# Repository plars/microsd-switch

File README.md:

## MicroSD Switch

This a derivative work of a similar project by Joel Fernandes.  You can find
his original works that this is based on at:
https://github.com/joelagnel/microsd-switch

The main changes I made were to use 2x4 IDC headers instead of 1x8 rows,
and I also removed the usb/ftdi based switching in favor of a 40pin
connector so that I could use it as a RPI2/3 hat. It's not a proper hat
layout at the moment with eeprom or recommended board layout because it's
a work in progress, but the prototypes fit nicely as it is now.

To switch between host and target, it is currently wired to use GPIO 12

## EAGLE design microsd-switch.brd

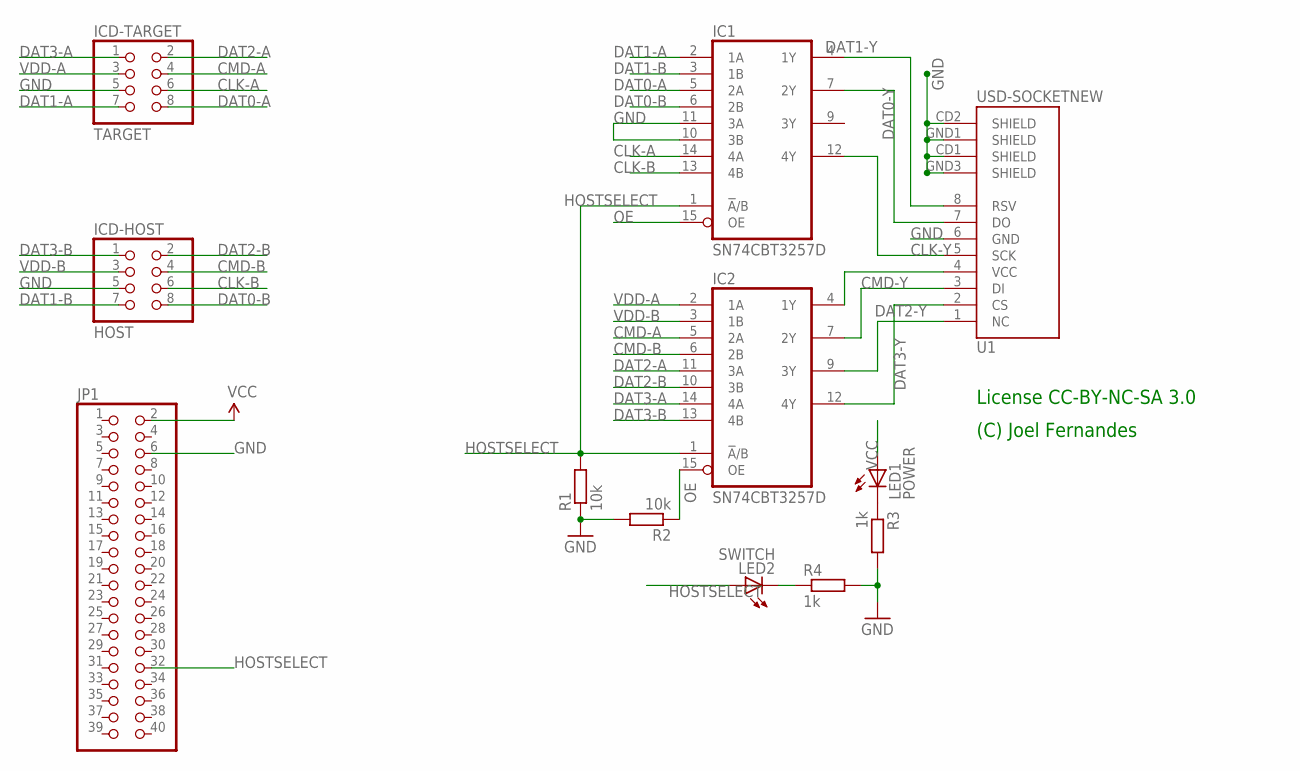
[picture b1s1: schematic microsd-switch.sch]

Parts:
IC1, IC2: SN74CBT3257D; SO16
ICD-HOST: HOST; 2X04
ICD-TARGET: TARGET; 2X04
JP1: PINHD-2X20; 2X20
LED1: POWER; CHIP-LED0805
LED2: SWITCH; CHIP-LED0805
R1, R2: 10k; R1206
R3, R4: 1k; R1206
U1: USD-SOCKETNEW; MICRO-SD-SOCKET-PP

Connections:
CLK-A: IC1.14 (4A), ICD-TARGET.6
CLK-B: IC1.13 (4B), ICD-HOST.6
CLK-Y: IC1.12 (4Y), U1.5 (SCK)
CMD-A: IC2.5 (2A), ICD-TARGET.4
CMD-B: IC2.6 (2B), ICD-HOST.4
CMD-Y: IC2.7 (2Y), U1.3 (DI)
DAT0-A: IC1.5 (2A), ICD-TARGET.8
DAT0-B: IC1.6 (2B), ICD-HOST.8
DAT0-Y: IC1.7 (2Y), U1.7 (DO)
DAT1-A: IC1.2 (1A), ICD-TARGET.7
DAT1-B: IC1.3 (1B), ICD-HOST.7
DAT1-Y: IC1.4 (1Y), U1.8 (RSV)
DAT2-A: IC2.11 (3A), ICD-TARGET.2
DAT2-B: IC2.10 (3B), ICD-HOST.2
DAT2-Y: IC2.9 (3Y), U1.1 (NC)
DAT3-A: IC2.14 (4A), ICD-TARGET.1
DAT3-B: IC2.13 (4B), ICD-HOST.1
DAT3-Y: IC2.12 (4Y), U1.2 (CS)
GND: IC1.8 (GND), IC1.10 (3B), IC1.11 (3A), IC2.8 (GND), ICD-HOST.5, ICD-TARGET.5, JP1.6, R1.1, R2.2, R3.2, R4.2, U1.6 (GND), U1.CD1 (SHIELD), U1.CD2 (SHIELD), U1.GND1 (SHIELD), U1.GND3 (SHIELD)
HOSTSELECT: IC1.1 (!A!/B), IC2.1 (!A!/B), JP1.32, LED2.A, R1.2
unnamed: IC2.4 (1Y), U1.4 (VCC)
unnamed: LED1.C, R3.1
unnamed: LED2.C, R4.1
OE: IC1.15 (OE), IC2.15 (OE), R2.1
VCC: IC1.16 (VCC), IC2.16 (VCC), JP1.2, LED1.A
VDD-A: IC2.2 (1A), ICD-TARGET.3
VDD-B: IC2.3 (1B), ICD-HOST.3

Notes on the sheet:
License CC-BY-NC-SA 3.0
(C) Joel Fernandes

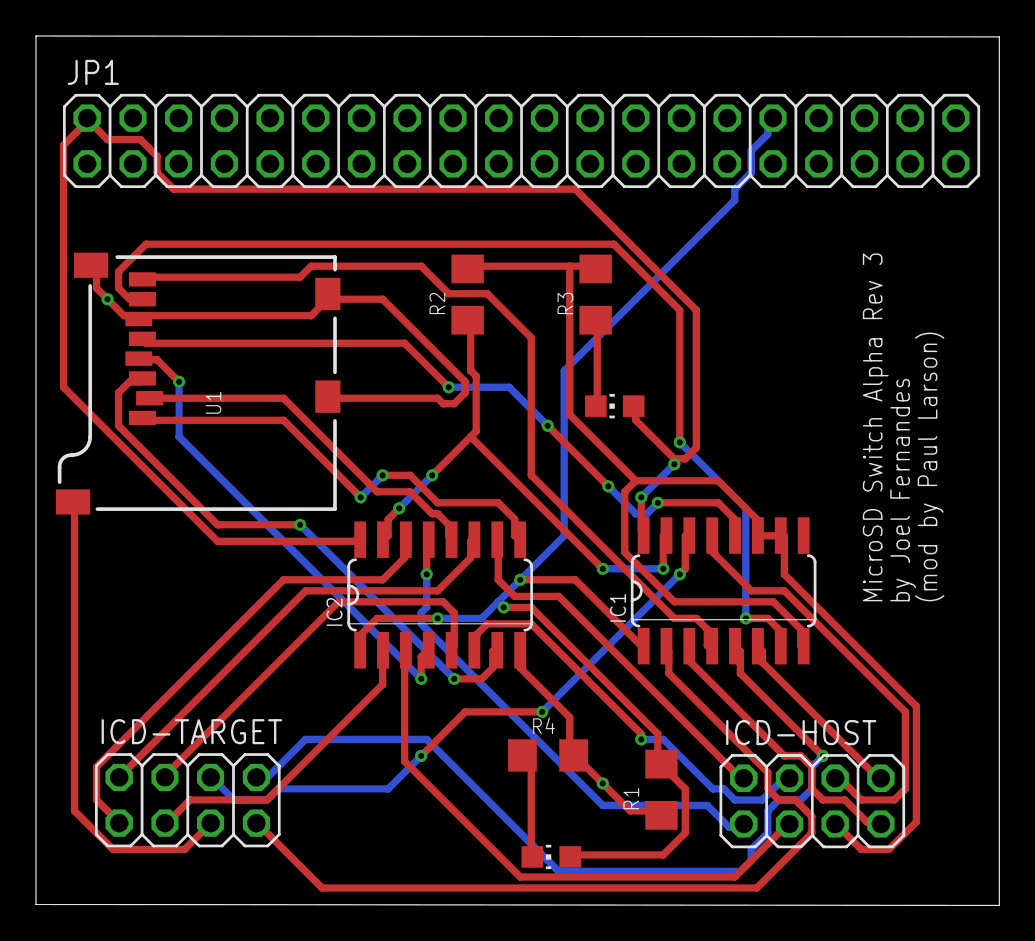
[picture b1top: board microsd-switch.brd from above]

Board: 2 copper layers, 53.5 x 48.3 mm, 12 parts (0 on the bottom side), 27 nets.

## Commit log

2017-06-21 MicroSD Switcher pi hat
2017-06-21 Add a photo of the pihat version
2017-06-21 corrected name in readme

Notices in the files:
parts and their libraries:
SparkFun: Licensing: CC v3.0 Share-Alike You are welcome to use this library for commercial purposes.
